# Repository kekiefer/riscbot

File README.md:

# RISCbot

Source files for the LoFive RISC-V RISCbot

## Building software

This project leverages the freedom-e-sdk bsp, and can use a toolchain that is
part of the freedom-e-sdk, or an external toolchain. You must define the
following environment variables to build the project:

```
export BSP_BASE=/my/desired/location/freedom-e-sdk/bsp
export RISCV_OPENOCD_PATH=/my/desired/location/openocd
export RISCV_PATH=/my/desired/location/riscv64-unknown-elf-gcc-<date>-<version>
```

After this, you can build the software as if you were building an example from the sdk:

```
make software upload PROGRAM=riscbot BOARD=freedom-e300-lofive
```

## Hardware design files

The directory `pcb` contains the KiCAD schematics used to prototype RISCbot.
Also included is a board layout that is complete to the best of my knowledge,
but please note that I have not actually fabricated this PCB as RISCbot was
hand-wired on a perforated circuit board.

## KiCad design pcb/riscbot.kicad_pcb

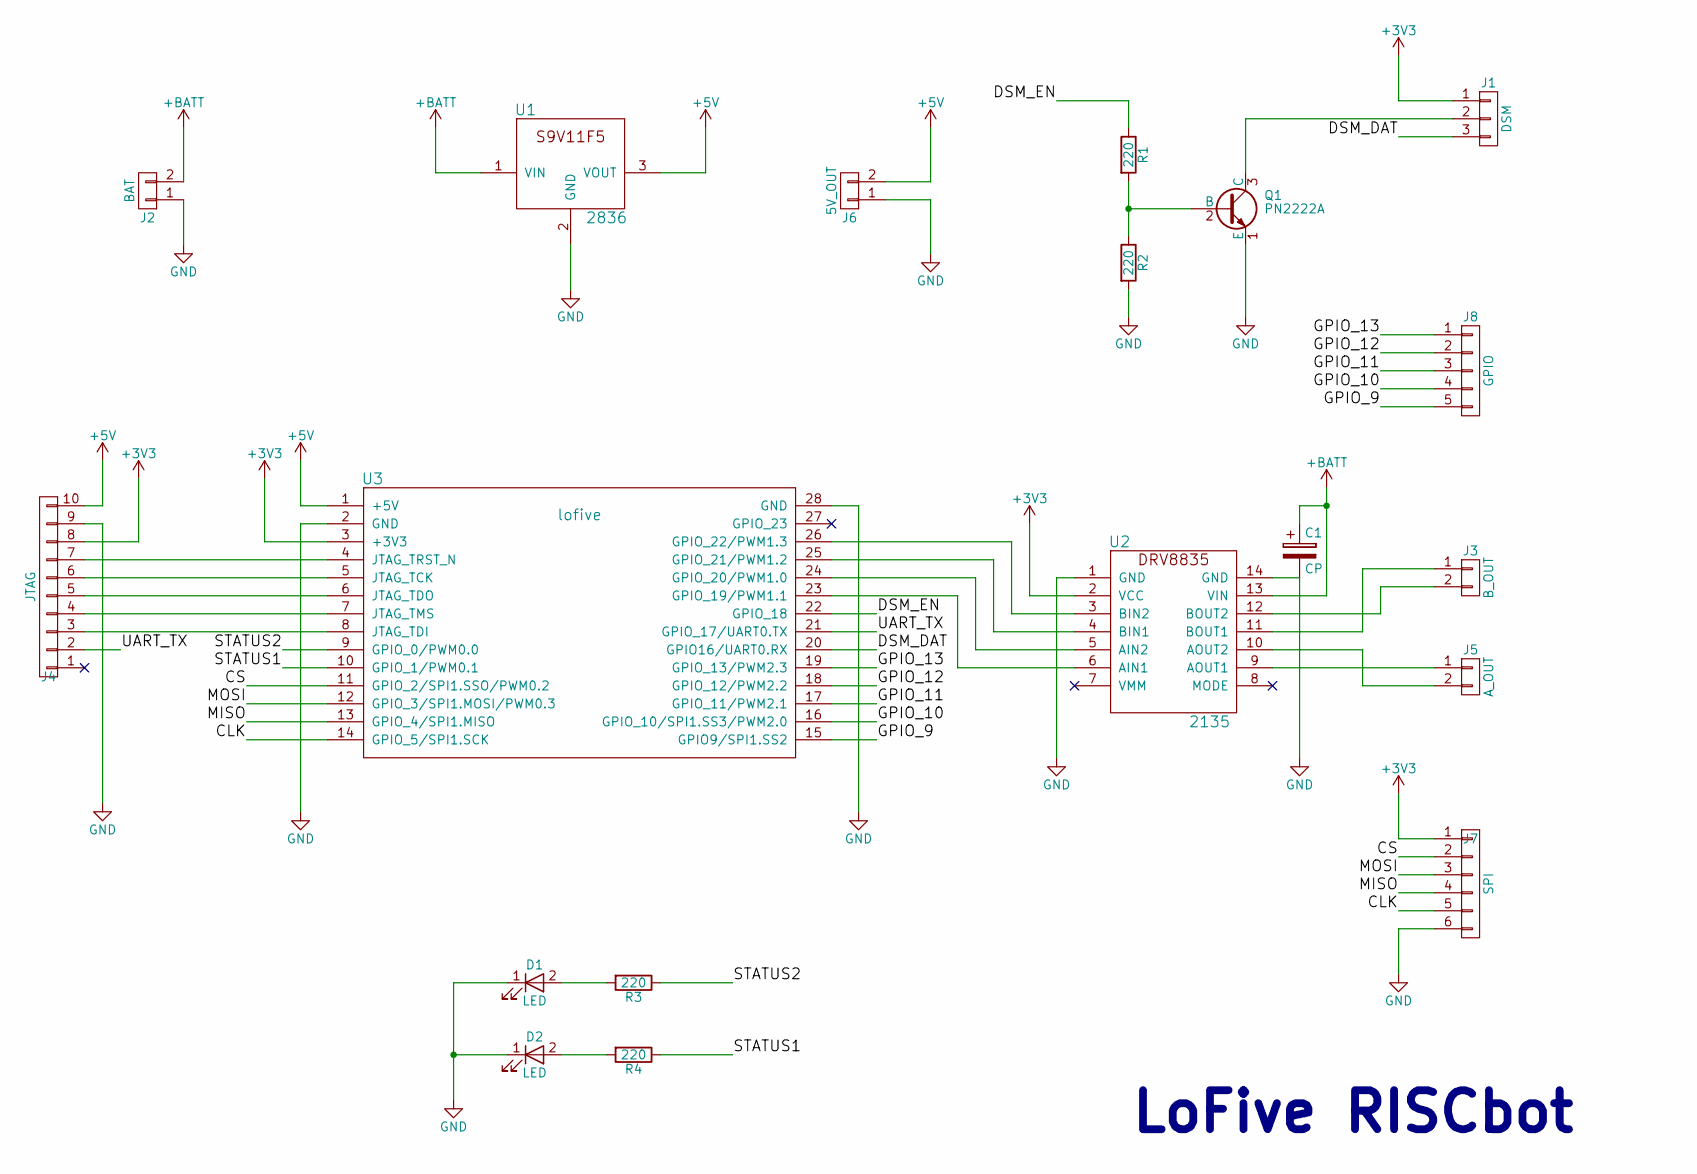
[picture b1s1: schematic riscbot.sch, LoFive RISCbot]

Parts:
C1: CP; CP_Radial_D5.0mm_P2.50mm
D1, D2: LED; LED_D5.0mm
J1: DSM; Pin_Header_Straight_1x03
J2: BAT; Pin_Header_Straight_1x02
J3: B_OUT; Pin_Header_Straight_1x02
J4: JTAG; Pin_Header_Straight_1x10
J5: A_OUT; Pin_Header_Straight_1x02
J6: 5V_OUT; Pin_Header_Straight_1x02
J7: SPI; Pin_Header_Straight_1x06
J8: GPIO; Pin_Header_Straight_1x05
Q1: PN2222A; TO-92_Inline_Wide
R1, R2, R3, R4: 220; R_Axial_DIN0207_L6.3mm_D2.5mm_P10.16mm_Horizontal
U1: 2836; s9V11f5
U2: 2135; drv8835-rev
U3: lofive

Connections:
+3V3: J1.1, J4.8, J7.1, U2.2 (VCC), U3.3 (+3V3)
+5V: J4.10, J6.2, U1.3 (VOUT), U3.1 (+5V)
+BATT: C1.1, J2.2, U1.1 (VIN), U2.13 (VIN)
/CLK: J7.5, U3.14 (GPIO_5/SPI1.SCK)
/CS: J7.2, U3.11 (GPIO_2/SPI1.SSO/PWM0.2)
/DSM_DAT: J1.3, U3.20 (GPIO16/UART0.RX)
/DSM_EN: R1.1, U3.22 (GPIO_18)
/GPIO_9: J8.5, U3.15 (GPIO9/SPI1.SS2)
/GPIO_10: J8.4, U3.16 (GPIO_10/SPI1.SS3/PWM2.0)
/GPIO_11: J8.3, U3.17 (GPIO_11/PWM2.1)
/GPIO_12: J8.2, U3.18 (GPIO_12/PWM2.2)
/GPIO_13: J8.1, U3.19 (GPIO_13/PWM2.3)
/MISO: J7.4, U3.13 (GPIO_4/SPI1.MISO)
/MOSI: J7.3, U3.12 (GPIO_3/SPI1.MOSI/PWM0.3)
/STATUS1: R4.1, U3.10 (GPIO_1/PWM0.1)
/STATUS2: R3.1, U3.9 (GPIO_0/PWM0.0)
/UART_TX: J4.2, U3.21 (GPIO_17/UART0.TX)
GND: C1.2, D1.1 (K), D2.1 (K), J2.1, J4.9, J6.1, J7.6, Q1.1 (E), R2.2, U1.2 (GND), U2.1 (GND), U2.14 (GND), U3.2 (GND), U3.28 (GND)
unnamed: D1.2 (A), R3.2
unnamed: D2.2 (A), R4.2
unnamed: J1.2, Q1.3 (C)
unnamed: J3.1, U2.11 (BOUT1)
unnamed: J3.2, U2.12 (BOUT2)
unnamed: J4.3, U3.8 (JTAG_TDI)
unnamed: J4.4, U3.7 (JTAG_TMS)
unnamed: J4.5, U3.6 (JTAG_TDO)
unnamed: J4.6, U3.5 (JTAG_TCK)
unnamed: J4.7, U3.4 (JTAG_TRST_N)
unnamed: J5.1, U2.9 (AOUT1)
unnamed: J5.2, U2.10 (AOUT2)
unnamed: Q1.2 (B), R1.2, R2.1
unnamed: U2.3 (BIN2), U3.26 (GPIO_22/PWM1.3)
unnamed: U2.4 (BIN1), U3.25 (GPIO_21/PWM1.2)
unnamed: U2.5 (AIN2), U3.24 (GPIO_20/PWM1.0)
unnamed: U2.6 (AIN1), U3.23 (GPIO_19/PWM1.1)

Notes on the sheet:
LoFive RISCbot

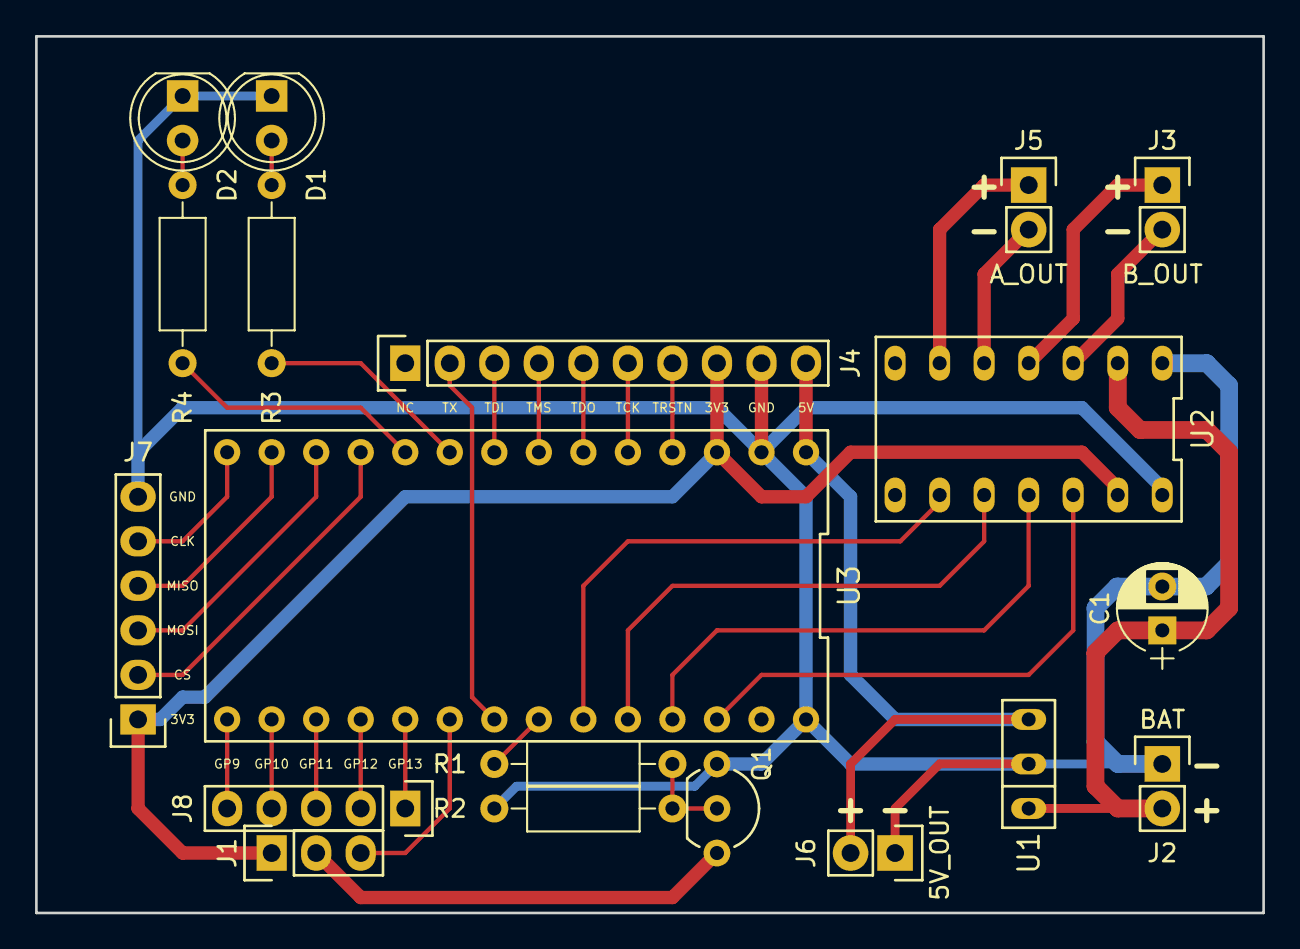
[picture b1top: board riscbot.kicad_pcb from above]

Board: 2 copper layers, 70.0 x 50.0 mm, 19 parts (0 on the bottom side), 35 nets.

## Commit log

2017-12-31 Initial commit of RISCbot
